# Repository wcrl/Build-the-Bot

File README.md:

# About WCRL
Our mission at the Watson Combat Robotics League is to empower collegiate students to develop technical engineering skills through competitive combat robotics. We aim to foster a community of innovation and creativity for students and enthusiasts by providing a platform for designing, building, and testing 3D printed robots in a safe and exciting environment. Our focus is on promoting STEM education by providing an opportunity for practical experience in mechanical design, electrical engineering, and programming as well as peer guidance and resources to make participation increasingly accessible. Through our league, we strive to cultivate the next generation of skilled engineers and innovators who will shape the future of technology and robotics.

# Build-the-Bot
Welcome to the Build-the-Bot platform! Build-the-Bot is an open-source Arduino based robotics platform maintained by the Watson Combat Robotics League at Binghamton University!

To get started, read the [Getting Started Guide](https://github.com/wcrl/Build-the-Bot/blob/453a59d6409c2aacc2f1eb8cd54fe76791a7de1f/Getting%20Started/Getting%20Started.md) and the [3D Printing Guide](https://github.com/wcrl/Build-the-Bot/blob/453a59d6409c2aacc2f1eb8cd54fe76791a7de1f/Getting%20Started/3D%20Printing%20Guide.md). From there, start designing and planning out your bot! 

### Check out our [Website](https://wcrl.github.io/)

### Join our [WCRL Discord](https://discord.gg/YJxM6xMASq)

In order to move to registered status and gain access to more channels make sure you
- Change your discord nickname in this server to your first and last name 
- Fill out our registration form via google forms: https://forms.gle/xkhhvzqmUq5xLZNm7

If you have any questions, please contact us via our discord, or email WCRL@binghamton.edu.

Happy Building!

# Future Development Plans 
- PCB for Battery Cutoff

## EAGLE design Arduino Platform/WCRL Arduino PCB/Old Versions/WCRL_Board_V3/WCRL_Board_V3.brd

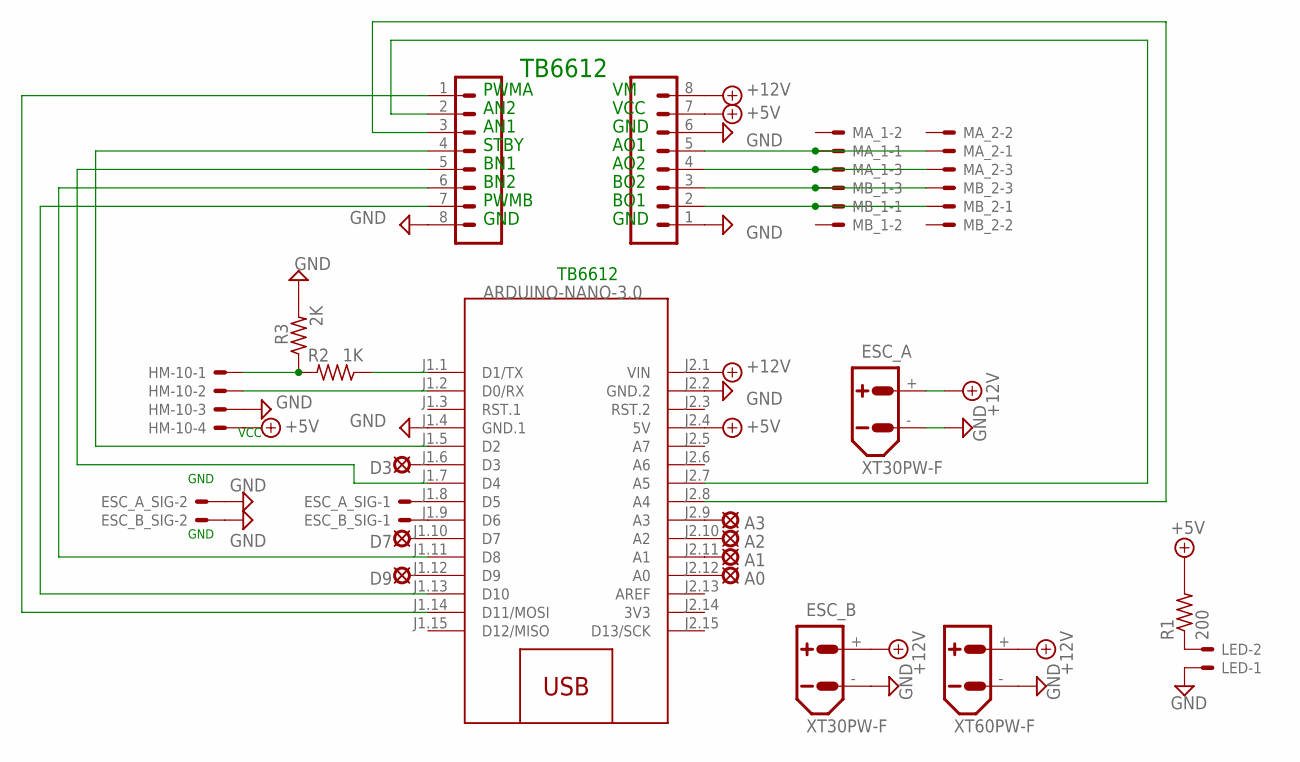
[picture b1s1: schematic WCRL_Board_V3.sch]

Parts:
A0, A1, A2, A3: LSP10
BATTERY: XT60PW-F
D3, D7, D9: LSP10
ESC_A: XT30PW-F
ESC_A_SIG: JST-XH-02-PIN-LONG-PAD; JST-XH-02-PACKAGE-LONG-PAD
ESC_B: XT30PW-F
ESC_B_SIG: JST-XH-02-PIN-LONG-PAD; JST-XH-02-PACKAGE-LONG-PAD
HM-10: JST-XH-04-PIN-LONG-PAD; JST-XH-04-PACKAGE-LONG-PAD
J1, J2: CONN_08NO_SILK_FEMALE_PTH; 1X08_NO_SILK
LED: JST-XH-02-PIN-LONG-PAD; JST-XH-02-PACKAGE-LONG-PAD
M1: ARDUINO-NANO-3.0
MA_1, MA_2: JST-XH-03-PIN-LONG-PAD; JST-XH-03-PACKAGE-LONG-PAD
MB_1, MB_2: JST-XH-03-PIN-LONG-PAD; JST-XH-03-PACKAGE-LONG-PAD
R1: 200; 0204/5
R2: 1K; 0204/5
R3: 2K; 0204/5

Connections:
3V3: M1.J2.14 (3V3)
+5V: HM-10.4, J1.7, M1.J2.4 (5V), R1.2
+12V: BATTERY.+, ESC_A.+, ESC_B.+, J1.8, M1.J2.1 (VIN)
GND: BATTERY.-, ESC_A.-, ESC_A_SIG.2, ESC_B.-, ESC_B_SIG.2, HM-10.3, J1.1, J1.6, J2.8, LED.1, M1.J1.4 (GND.1), M1.J2.2 (GND.2), R3.2
unnamed: D3.MP, M1.J1.6 (D3)
unnamed: D7.MP, M1.J1.10 (D7)
unnamed: D9.MP, M1.J1.12 (D9)
unnamed: HM-10.1, R2.2, R3.1
unnamed: ESC_A_SIG.1, M1.J1.8 (D5)
unnamed: ESC_B_SIG.1, M1.J1.9 (D6)
unnamed: M1.J1.1 (D1/TX), R2.1
unnamed: J2.4, M1.J1.5 (D2)
unnamed: J2.3, M1.J2.8 (A4)
unnamed: J1.5, MA_1.1, MA_2.1
unnamed: J1.4, MA_1.3, MA_2.3
unnamed: J1.2, MB_1.1, MB_2.1
unnamed: J1.3, MB_1.3, MB_2.3
unnamed: HM-10.2, M1.J1.2 (D0/RX)
unnamed: J2.2, M1.J2.7 (A5)
unnamed: J2.5, M1.J1.7 (D4)
unnamed: J2.6, M1.J1.11 (D8)
unnamed: LED.2, R1.1
unnamed: J2.7, M1.J1.13 (D10)
unnamed: J2.1, M1.J1.14 (D11/MOSI)
unnamed: A3.MP, M1.J2.9 (A3)
unnamed: A1.MP, M1.J2.11 (A1)
unnamed: A0.MP, M1.J2.12 (A0)
unnamed: A2.MP, M1.J2.10 (A2)

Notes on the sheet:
PWMA
GND
VCC
AO1
AO2
BO2
BO1
AN2
AN1
STBY
BN1
BN2
PWMB
TB6612

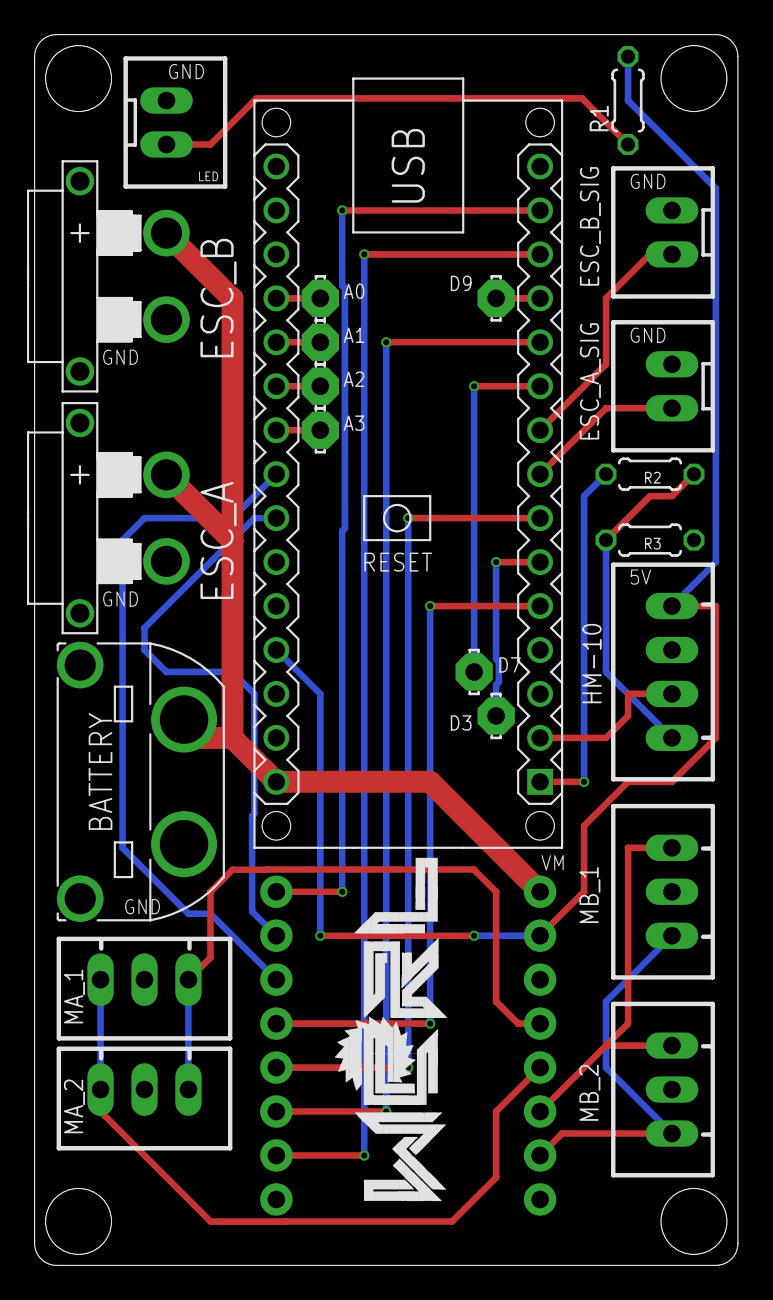
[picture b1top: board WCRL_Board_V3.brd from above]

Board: 2 copper layers, 40.6 x 71.1 mm, 24 parts (1 on the bottom side), 27 nets.

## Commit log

2022-09-14 Adding PCB V2
2022-09-14 Adding in PCB BOM
2022-09-14 Moving BOM
2022-09-14 Trying ODS
2022-09-14 Removing failed BOMs
2022-09-15 Add Board V3
2022-09-15 Create Changelog
2022-09-16 Added getting started document
2022-09-16 Revised documentation
2022-09-16 Add BOM
2022-09-16 Update BOM
2022-09-16 Updating Documentation
2022-09-16 Transferring Code
2022-09-20 Addition of Pictures
    Finding it difficult becoming accustomed to Git and GitHub. Spent too long thinking there was a complicated way to insert the photos and learned there was an upload spot. I have no idea how to size t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
2022-09-23 Update 3D Printing Guide.md
    Swap baby groot for sc of stump print. Addition or PETG option because same price as PLA at ETS
2022-09-23 Updated BOM with new links
2022-09-23 Modernize code and reorganize
2022-09-23 Update code comments
2022-09-24 Add Motor Driver Arduino Library
    added sparkfun tb6612 motor driver arduino library
2022-09-24 Create Libraries folder
    created libraries folder
2022-09-24 Add motor driver libraries
    added TB6612FNG motor driver library zip file
2022-09-24 Create README.txt
    Additional instructions for using Arduino libraries
2022-10-19 Update Bot_with_One_Competition_Attachment.ino
    All I did was add a note to the code reminding that Arduino code cannot be uploaded while dabble is active and slightly change the weapon speed values in case Dillon's hunch is right.
2022-10-28 Update Bot_with_Two_Competition_Attachments.ino
    edit typo in comment
2022-11-10 Add PCB v3 Images
2022-11-11 Create Troubleshooting
2022-11-11 Rule revisions
2022-11-12 Create Electronics
2022-11-12 Update and rename Electronics to Electrical_Troubleshooting
2022-11-12 Update Electrical_Troubleshooting
2022-11-12 Update and rename Electrical_Troubleshooting to Electronics_Troubleshooting
2022-11-12 Update Electronics_Troubleshooting
2022-12-02 Create Coding_Troubleshooting
2022-12-13 Rename Troubleshooting/Electronics_Troubleshooting.md to Troubleshooting/Getting Started/Electronics_Troubleshooting.md
2022-12-13 Rename Troubleshooting/Getting Started/Electronics_Troubleshooting.md to Electronics_Troubleshooting.md
2022-12-13 Rename Electronics_Troubleshooting.md to Getting Started/Electronics_Troubleshooting.md
2023-01-13 Spring 2023 Rule Revisions
2023-02-15 Added support for BitBlue
2023-03-25 Add BBB
2023-03-30 Added V4
2023-08-26 Rename WCRL 2022-2023 Rulebook.md to WCRL 2023-2024 Rulebook.md
2023-09-12 Update README.md
    Fixed Discord invite link
2023-09-29 Update Electronics BOM.md
    Luke R.
2023-10-06 L298N_Schematic
    Schematic for the L298N motor driver, pictures included for clarification to make it fit with the V3 PCB
2023-10-22 L298 Schematic image
    Little easier to view than opening up Eagle or Fusion
2024-02-06 Add files via upload
    Autonomous Wiring, both pdf and actual schematic file for easier viewing
2024-03-12 Branch for trapdoor code to be added for arena
2024-03-12 Files Reorganized and Named
2024-03-12 Branch for arena code to be available (#44)
    * Branch for trapdoor code to be added for arena
    * Files Reorganized and Named
2024-03-15 arena code for 2 servos and brushless motor
2024-03-15 arena code for 2 servos and brushless motor (#45)
2024-03-18 update (#46)
2024-09-08 Updated and Organized
    Platform Separation alongside main parts library
2024-09-08 Simplify
    Sample Bod CAD into Getting Started
2024-09-12 Created New Rules
2024-09-12 Update WCRL 2024-2025 Rulebook.md
    Minor Rules Update
2024-09-19 Added Pico W Schematic
2024-09-19 Restore DS Store
2024-09-19 Gitignore
2024-10-16 Added micropython code for PICO_W
    WIFI name PicoW_Gamepad_Control
    password 123456789
2024-10-18 Created Code folder
    To create: electronics
2024-10-18 Electrical
    Added more Pico W files
    Updated Readme
2025-02-16 Update WCRL 2024-2025 Rulebook.md
    Reinstate John as chairperson, put Mack back to build tech
2025-02-16 Update WCRL 2024-2025 Rulebook.md
    Definition of autonomous updated to match SPARC definition
2025-02-16 Update WCRL 2024-2025 Rulebook.md
    Updated prohibited weapons to be more specific and match SPARC
2025-02-20 added bluetooth controller code - credit to aadhi
2025-02-23 Update WCRL 2024-2025 Rulebook.md
    Mobility Rules- Defined rolling robots
    Weapon- Spinning weapons need to stop in 60 sec
2025-02-25 Update WCRL 2024-2025 Rulebook.md
    removed autonomy prohiting rules (i.e. autonomous bots are allowe dnow)
2025-02-25 updated folder name
2025-03-17 Update WCRL 2024-2025 Rulebook.md
    nomenclature

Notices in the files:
parts and their libraries:
SparkFun-Connectors: Licensing: Creative Commons ShareAlike 4.0 International - https://creativecommons.org/licenses/by-sa/4.0
diy-modules: Released under the Creative Commons Attribution 4.0 International License: http://creativecommons.org/licenses/by/4.0
